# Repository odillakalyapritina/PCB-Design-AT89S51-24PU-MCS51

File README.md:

# PCB-Design-AT89S51-24PU-MCS51

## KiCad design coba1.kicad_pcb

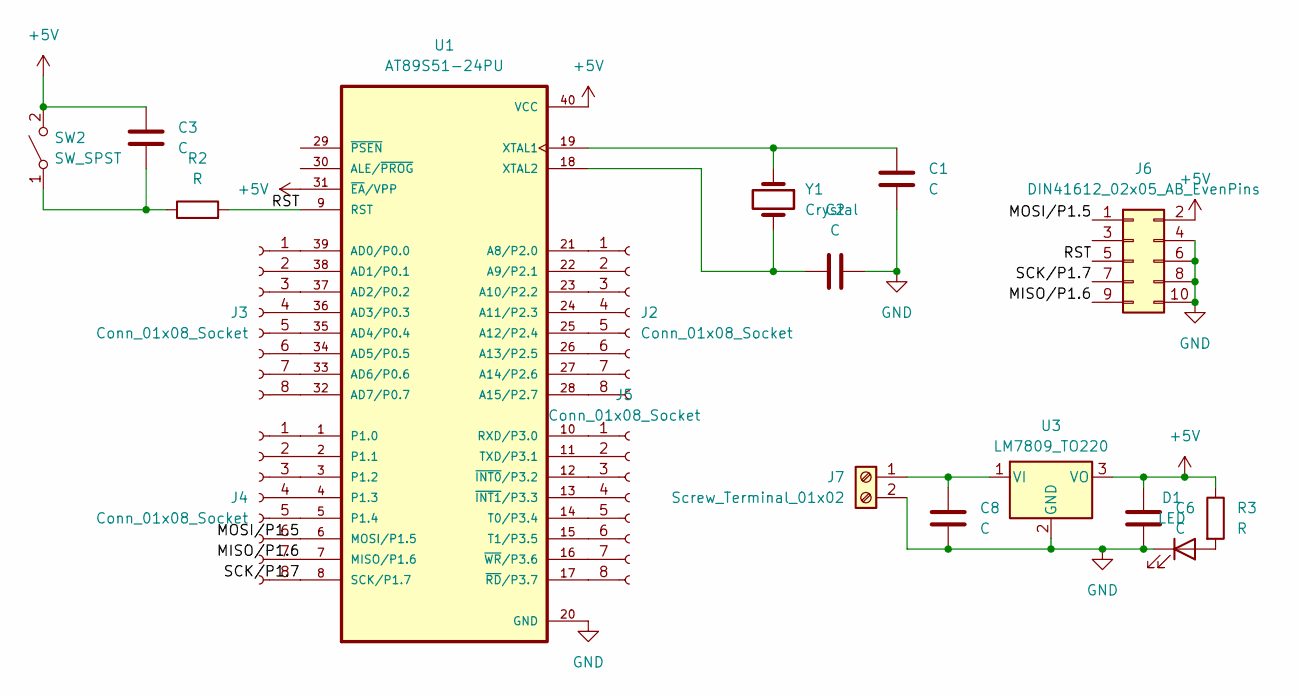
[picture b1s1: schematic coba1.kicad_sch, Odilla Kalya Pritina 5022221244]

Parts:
C1, C2: C; C_Disc_D5.1mm_W3.2mm_P5.00mm
C3, C6, C8: C; CP_Radial_D4.0mm_P2.00mm
D1: LED; LED_D3.0mm
J2, J3, J4, J5: Conn_01x08_Socket; PinHeader_1x08_P2.54mm_Vertical
J6: DIN41612_02x05_AB_EvenPins; IDC-Header_2x05_P2.54mm_Vertical
J7: Screw_Terminal_01x02; TerminalBlock_Phoenix_MKDS-1,5-2_1x02_P5.00mm_Horizontal
R2, R3: R; R_Axial_DIN0204_L3.6mm_D1.6mm_P7.62mm_Horizontal
SW2: SW_SPST; SW_PUSH_6mm
U1: AT89S51-24PU; DIP-40_W15.24mm; PARTREV B
U3: LM7809_TO220; TO-220-3_Vertical
Y1: Crystal; Crystal_HC49-4H_Vertical

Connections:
+5V: C3.1, C6.1, J6.2 (Pin_b2), R3.1, SW2.2 (B), U1.31 (~EA/VPP), U1.40 (VCC), U3.3 (VO)
/MISO/P1.6: J4.7, J6.9 (Pin_a10), U1.7 (MISO/P1.6)
/MOSI/P1.5: J4.6, J6.1 (Pin_a2), U1.6 (MOSI/P1.5)
/RST: J6.5 (Pin_a6), R2.2, U1.9 (RST)
/SCK/P1.7: J4.8, J6.7 (Pin_a8), U1.8 (SCK/P1.7)
GND: C1.2, C2.1, C6.2, C8.2, D1.1 (K), J6.4 (Pin_b4), J6.6 (Pin_b6), J6.8 (Pin_b8), J6.10 (Pin_b10), J7.2, U1.20 (GND), U3.2 (GND)
unnamed: D1.2 (A), R3.2
unnamed: J2.1, U1.21 (A8/P2.0)
unnamed: J2.2, U1.22 (A9/P2.1)
unnamed: J2.3, U1.23 (A10/P2.2)
unnamed: J2.4, U1.24 (A11/P2.3)
unnamed: J2.5, U1.25 (A12/P2.4)
unnamed: J2.6, U1.26 (A13/P2.5)
unnamed: J2.7, U1.27 (A14/P2.6)
unnamed: J2.8, U1.28 (A15/P2.7)
unnamed: J3.1, U1.39 (AD0/P0.0)
unnamed: J3.2, U1.38 (AD1/P0.1)
unnamed: J3.3, U1.37 (AD2/P0.2)
unnamed: J3.4, U1.36 (AD3/P0.3)
unnamed: J3.5, U1.35 (AD4/P0.4)
unnamed: J3.6, U1.34 (AD5/P0.5)
unnamed: J3.7, U1.33 (AD6/P0.6)
unnamed: J3.8, U1.32 (AD7/P0.7)
unnamed: J4.1, U1.1 (P1.0)
unnamed: J4.2, U1.2 (P1.1)
unnamed: J4.3, U1.3 (P1.2)
unnamed: J4.4, U1.4 (P1.3)
unnamed: J4.5, U1.5 (P1.4)
unnamed: J5.1, U1.10 (RXD/P3.0)
unnamed: J5.2, U1.11 (TXD/P3.1)
unnamed: J5.3, U1.12 (~INT0/P3.2)
unnamed: J5.4, U1.13 (~INT1/P3.3)
unnamed: J5.5, U1.14 (T0/P3.4)
unnamed: J5.6, U1.15 (T1/P3.5)
unnamed: J5.7, U1.16 (~WR/P3.6)
unnamed: J5.8, U1.17 (~RD/P3.7)
unnamed: C8.1, J7.1, U3.1 (VI)
unnamed: C3.2, R2.1, SW2.1 (A)
unnamed: C1.1, U1.19 (XTAL1), Y1.1
unnamed: C2.2, U1.18 (XTAL2), Y1.2

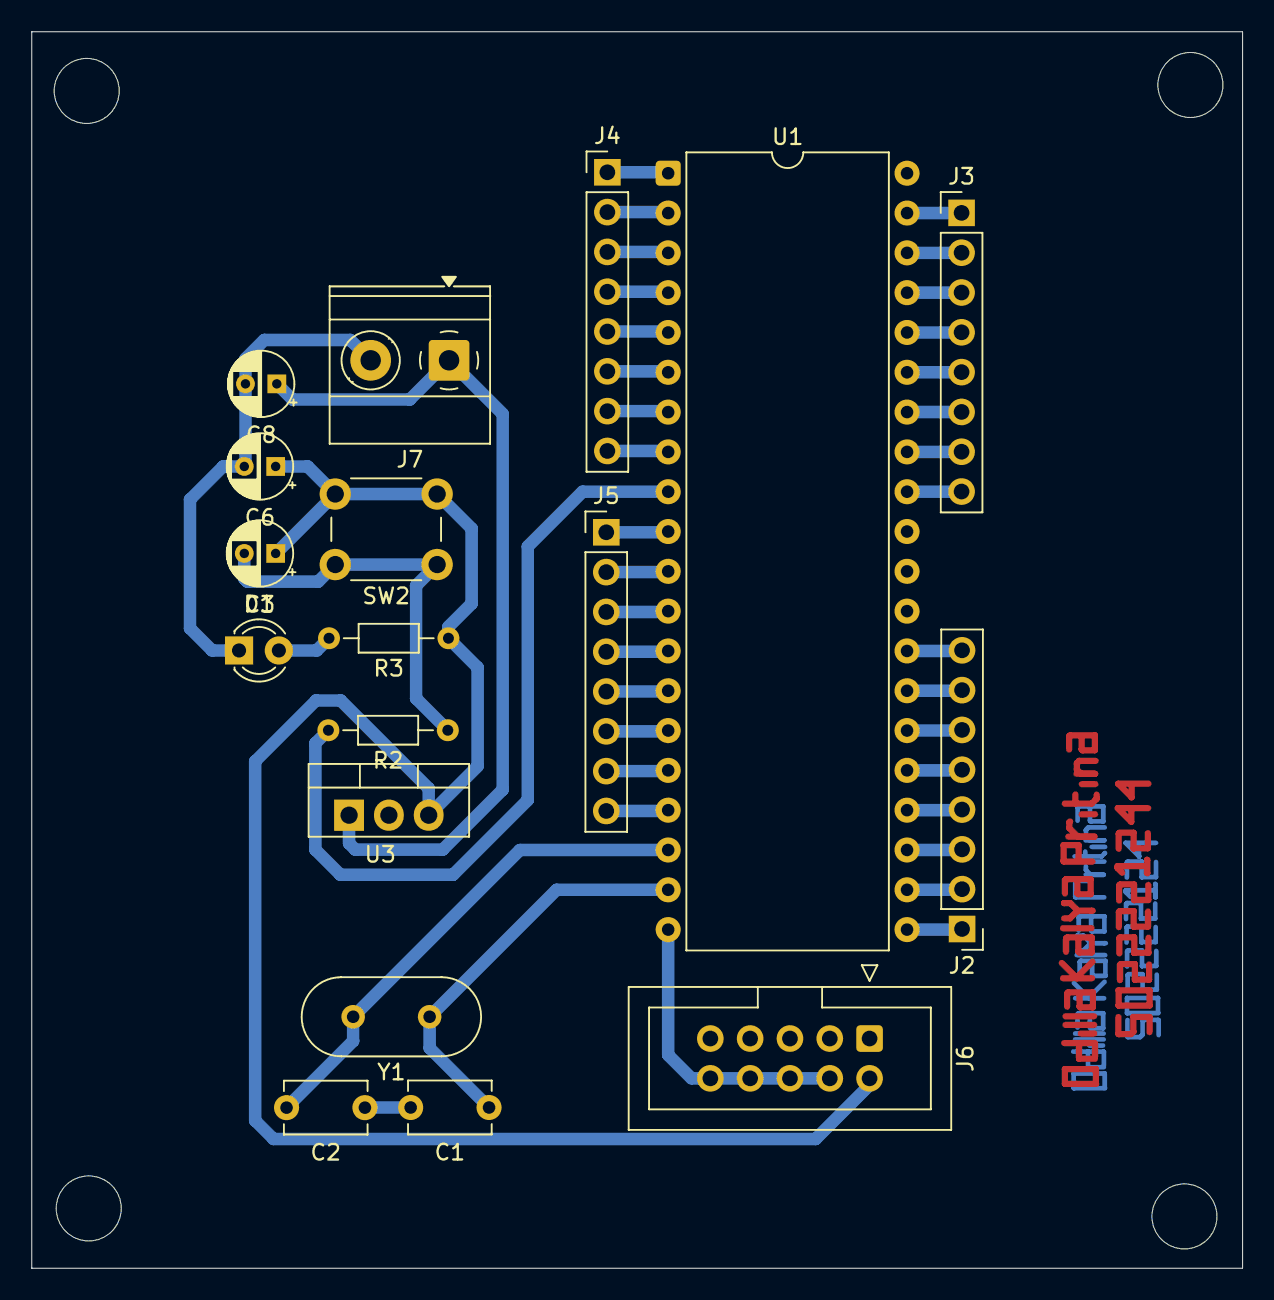
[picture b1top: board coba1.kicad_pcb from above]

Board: 2 copper layers, 77.3 x 78.9 mm, 18 parts (0 on the bottom side), 40 nets.

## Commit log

2025-08-27 README.md
